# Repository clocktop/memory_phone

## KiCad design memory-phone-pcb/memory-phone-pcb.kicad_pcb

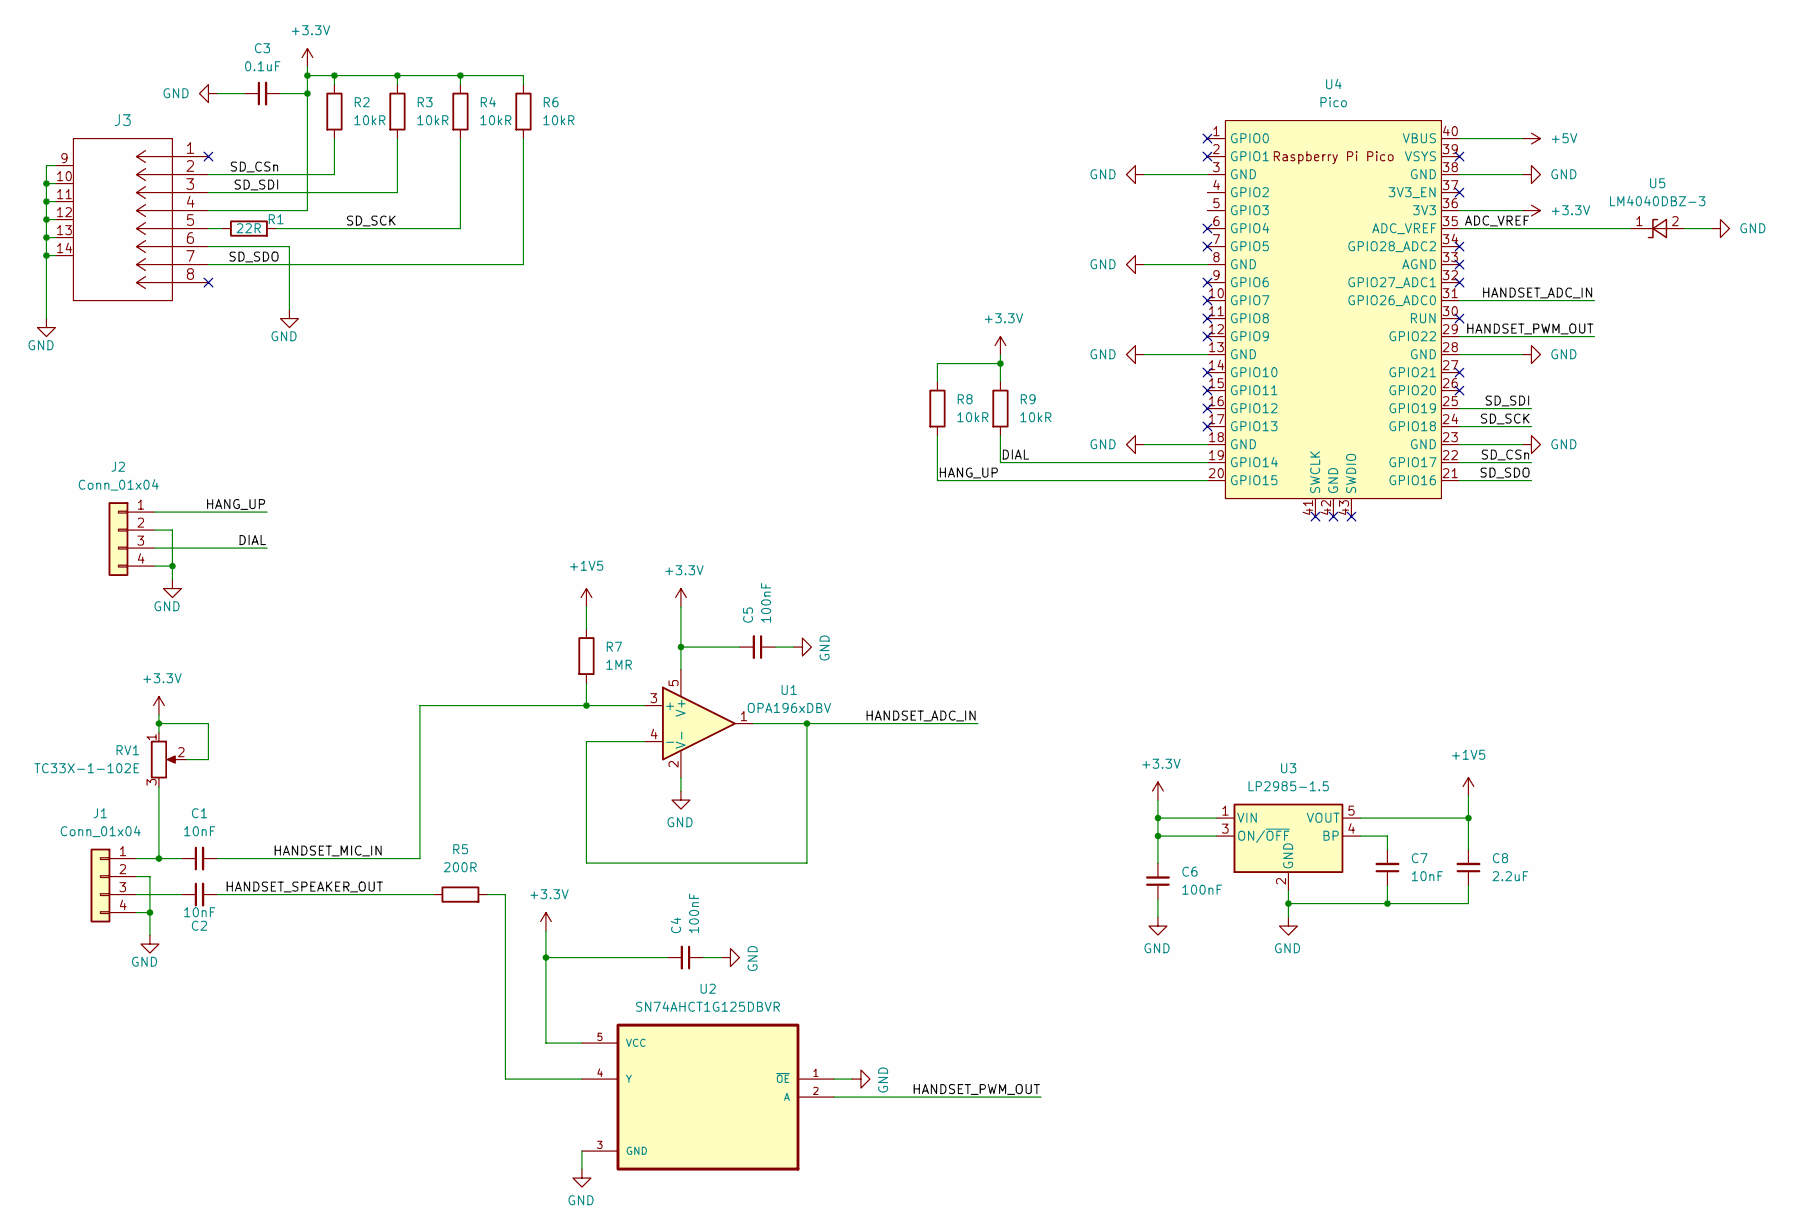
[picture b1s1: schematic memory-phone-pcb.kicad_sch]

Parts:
C1, C2, C7: 10nF; C_0603_1608Metric_Pad1.08x0.95mm_HandSolder
C3: 0.1uF; C_0603_1608Metric_Pad1.08x0.95mm_HandSolder
C4, C5, C6: 100nF; C_0603_1608Metric_Pad1.08x0.95mm_HandSolder
C8: 2.2uF; C_0603_1608Metric_Pad1.08x0.95mm_HandSolder
J1, J2: Conn_01x04; PinSocket_1x04_P2.54mm_Vertical
J3: DM3D-SF
R1: 22R; R_0603_1608Metric_Pad0.98x0.95mm_HandSolder
R2, R3, R4, R6, R8, R9: 10kR; R_0603_1608Metric_Pad0.98x0.95mm_HandSolder
R5: 200R; R_0603_1608Metric_Pad0.98x0.95mm_HandSolder
R7: 1MR; R_0603_1608Metric_Pad0.98x0.95mm_HandSolder
RV1: TC33X-1-102E; TC33X-1
U1: OPA196xDBV; SOT-23-5
U2: SN74AHCT1G125DBVR; SOT-23-5_HandSoldering
U3: LP2985-1.5; SOT-23-5
U4: Pico; RPi_Pico_SMD_TH
U5: LM4040DBZ-3; SOT-23

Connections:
+1V5: C8.2, R7.1, U3.5 (VOUT)
+3V3: C3.2, C4.2, C5.2, C6.2, J3.4, R2.1, R3.1, R4.1, R6.1, R8.1, R9.1, RV1.1, RV1.2, U1.5 (V+), U2.5 (VCC), U3.1 (VIN), U3.3 (ON/~OFF), U4.36 (3V3)
+5V: U4.40 (VBUS)
/ADC_VREF: U4.35 (ADC_VREF), U5.1 (K)
/DIAL: J2.3, R9.2, U4.19 (GPIO14)
/HANDSET_ADC_IN: U1.1, U1.4 (-), U4.31 (GPIO26_ADC0)
/HANDSET_MIC_IN: C1.2, R7.2, U1.3 (+)
/HANDSET_PWM_OUT: U2.2 (A), U4.29 (GPIO22)
/HANDSET_SPEAKER_OUT: C2.2, R5.1
/HANG_UP: J2.1, R8.2, U4.20 (GPIO15)
/SD_CSn: J3.2, R2.2, U4.22 (GPIO17)
/SD_SCK: R1.2, R4.2, U4.24 (GPIO18)
/SD_SDI: J3.3, R3.2, U4.25 (GPIO19)
/SD_SDO: J3.7, R6.2, U4.21 (GPIO16)
GND: C3.1, C4.1, C5.1, C6.1, C7.1, C8.1, J1.2, J1.4, J2.2, J2.4, J3.6, J3.9 (GND), J3.10 (GND), J3.11 (GND), J3.12 (GND), J3.13 (GND), J3.14 (GND), U1.2 (V-), U2.1 (~OE), U2.3 (GND), U3.2 (GND), U4.3 (GND), U4.8 (GND), U4.13 (GND), U4.18 (GND), U4.23 (GND), U4.28 (GND), U4.38 (GND), U5.2 (A)
unnamed: C1.1, J1.1, RV1.3
unnamed: C2.1, J1.3
unnamed: C7.2, U3.4 (BP)
unnamed: J3.5, R1.1
unnamed: R5.2, U2.4 (Y)

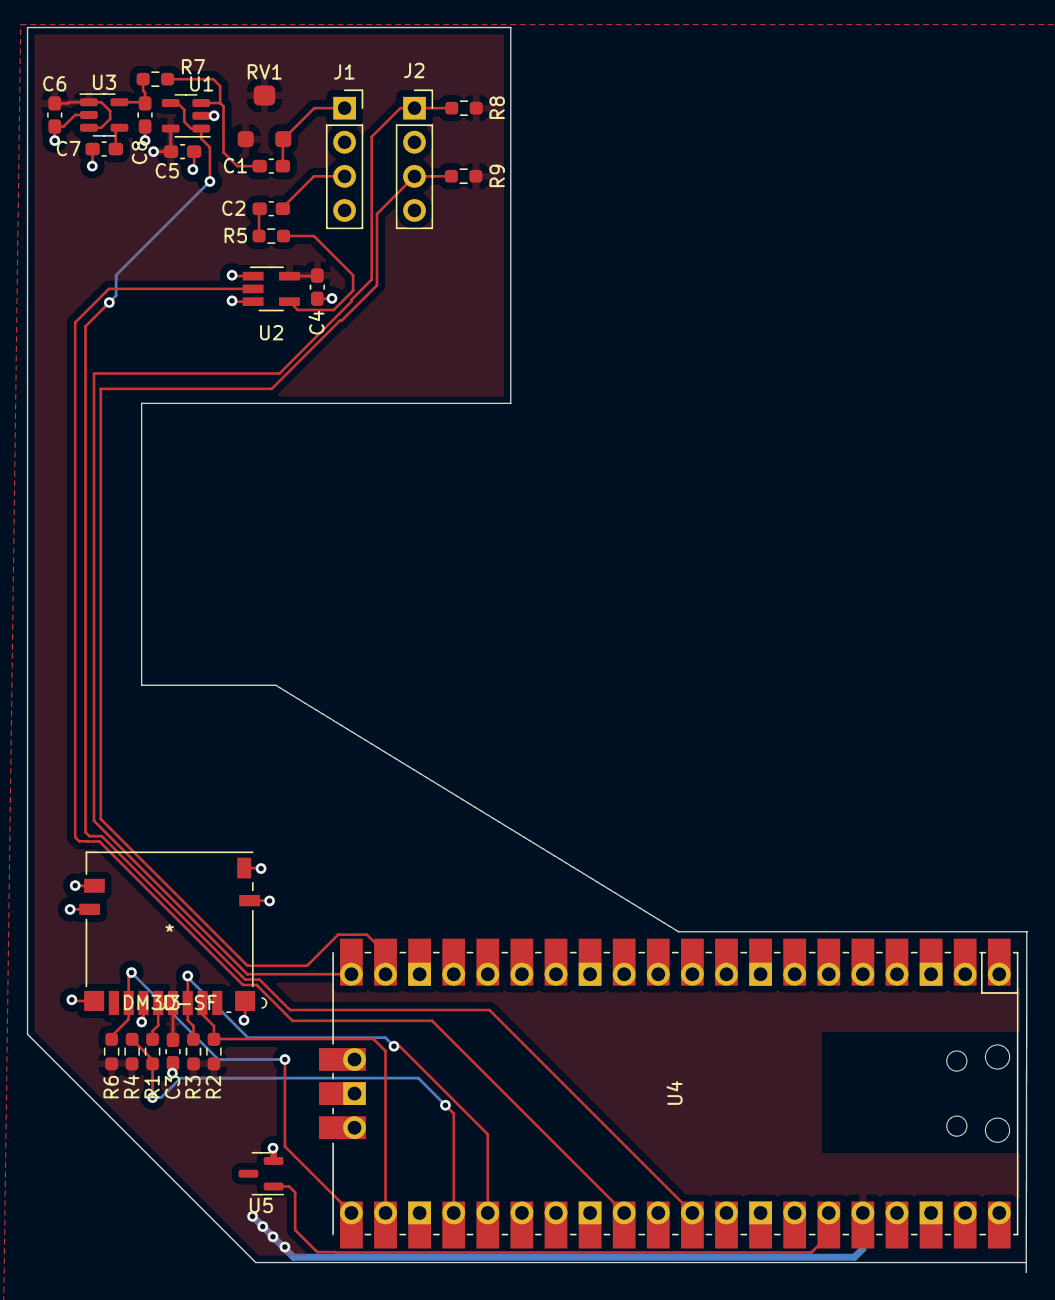
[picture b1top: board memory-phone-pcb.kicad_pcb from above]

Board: 2 copper layers, 74.5 x 92.7 mm, 26 parts (0 on the bottom side), 19 nets.

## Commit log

2022-03-20 first commit, adding kicad project
2022-03-20 sch work adding rp2040
2022-06-11 finished pcb
2022-06-11 blink test to build rpi code
2022-06-11 sd test
2022-06-11 making fixes
2022-06-23 catch up
2022-06-23 added lib files
2022-06-23 interrupt structure for hangup
2022-06-24 start of state machine for logging app
2022-06-24 now plays greeting message before adc starts, start and stop

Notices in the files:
parts and their libraries:
Copyright 2021 Accelerated Designs. All rights reserved.
